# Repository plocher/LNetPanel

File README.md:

# LNetPanel
## License: CERN Open Hardware Licence v1.2

LNetPanel - a distribution panel for LocoNet distribution

Optional 12v RailSync power injection, passthrough

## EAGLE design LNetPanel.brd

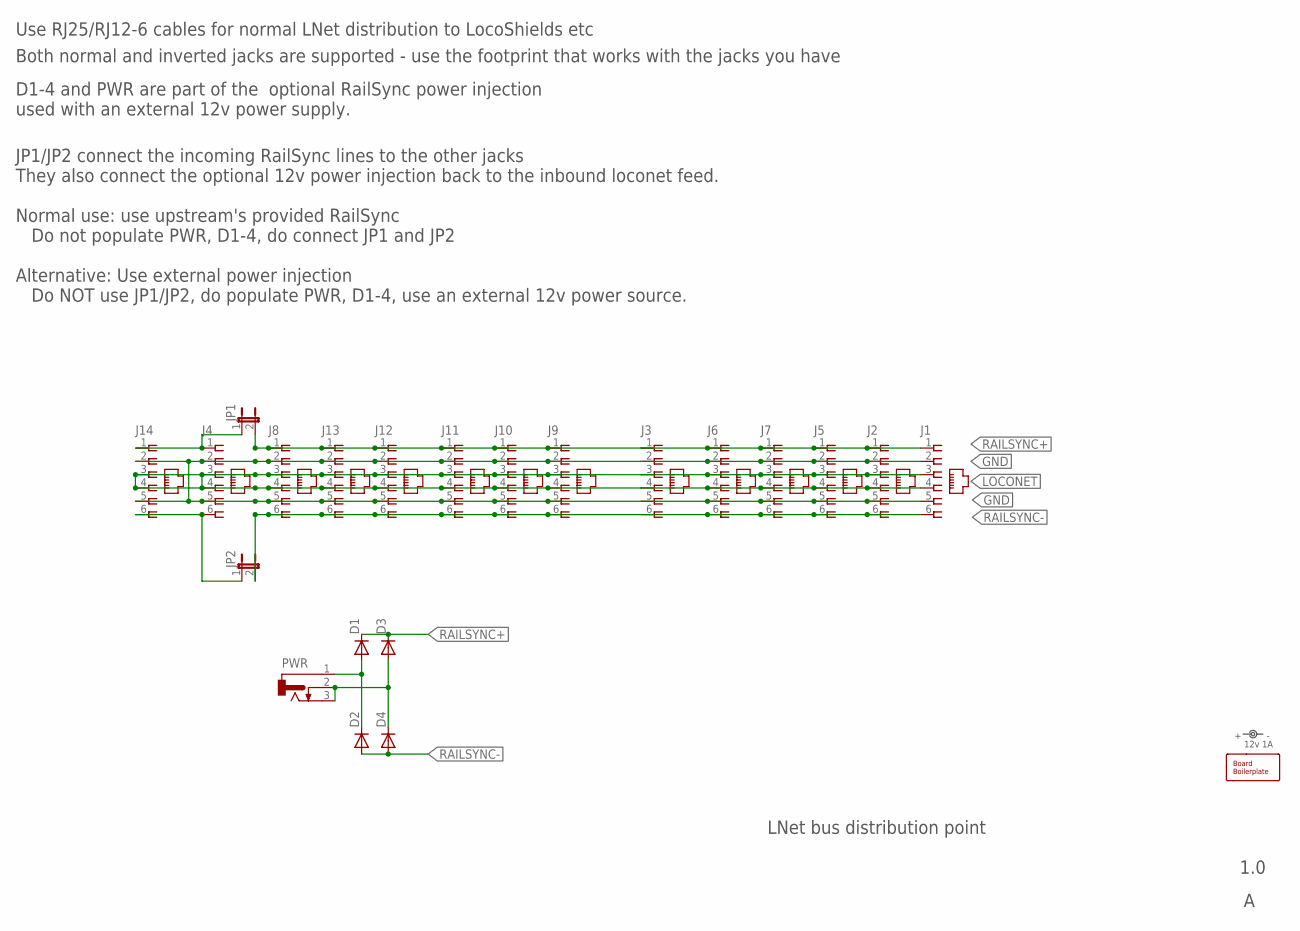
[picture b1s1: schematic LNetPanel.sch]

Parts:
D1, D2, D3, D4: DIODEPTH; DIODE-1N4001
J1, J2, J3, J4, J5, J6, J7: CONNECTOR-RJ25-43860-2-MOLEX; RJ25-INVERTED
J8, J9, J10, J11, J12, J13, J14: CONNECTOR-RJ25AMP; RJ25-PANEL
JP1, JP2: JUMPER-2PTH_LOCK; 1X02_LOCK
PWR: CONNECTOR-DC-POWER-RA; DCJ0202
U$1: BOARD50X50-HOHOLES; BOARD-SEEED7X7
U$2: 12v 1A; POWER_USAGE

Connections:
GND: J1.2, J1.5, J2.2, J2.5, J3.2, J3.5, J4.2, J4.5, J5.2, J5.5, J6.2, J6.5, J7.2, J7.5, J8.2, J8.5, J9.2, J9.5, J10.2, J10.5, J11.2, J11.5, J12.2, J12.5, J13.2, J13.5, J14.2, J14.5
LOCONET: J1.3, J1.4, J2.3, J2.4, J3.3, J3.4, J4.3, J4.4, J5.3, J5.4, J6.3, J6.4, J7.3, J7.4, J8.3, J8.4, J9.3, J9.4, J10.3, J10.4, J11.3, J11.4, J12.3, J12.4, J13.3, J13.4, J14.3, J14.4
unnamed: D3.A, D4.C, PWR.2, PWR.3
unnamed: D1.A, D2.C, PWR.1
unnamed: J4.1, J14.1, JP1.1
unnamed: J4.6, J14.6, JP2.1
RAILSYNC+: D1.C, D3.C, J1.1, J2.1, J3.1, J5.1, J6.1, J7.1, J8.1, J9.1, J10.1, J11.1, J12.1, J13.1, JP1.2
RAILSYNC-: D2.A, D4.A, J1.6, J2.6, J3.6, J5.6, J6.6, J7.6, J8.6, J9.6, J10.6, J11.6, J12.6, J13.6, JP2.2

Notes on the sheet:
1.0
LNet bus distribution point
Use RJ25/RJ12-6 cables for normal LNet distribution to LocoShields etc
D1-4 and PWR are part of the optional RailSync power injection used with an external 12v power supply.
Both normal and inverted jacks are supported - use the footprint that works with the jacks you have
JP1/JP2 connect the incoming RailSync lines to the other jacks They also connect the optional 12v power injection back to the inbound loconet feed. Normal use: use upstream's provided RailSync Do not populate PWR, D1-4, do connect JP1 and JP2 Alternative: Use external power injection Do NOT use JP1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

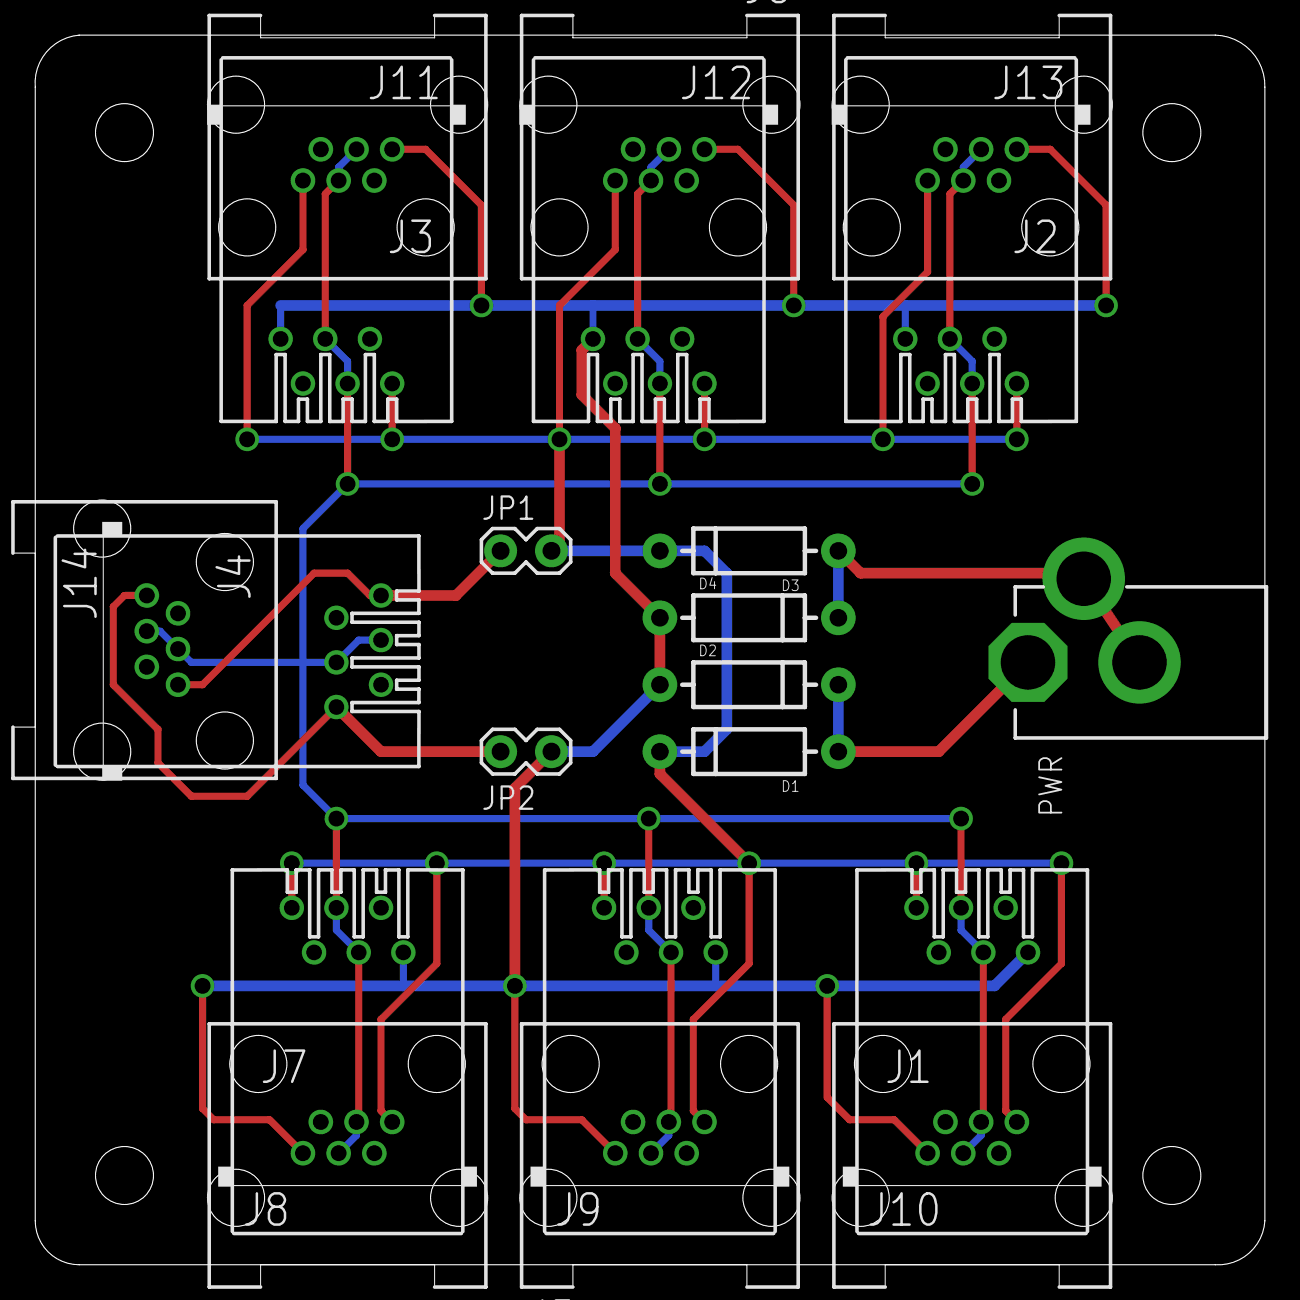
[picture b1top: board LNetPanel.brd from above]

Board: 2 copper layers, 70.0 x 70.0 mm, 23 parts (0 on the bottom side), 8 nets.

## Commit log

2022-11-18 Initial version
